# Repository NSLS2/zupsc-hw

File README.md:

# ZuPSC – NSLS-II Power Supply Controller

The **ZuPSC** is the next-generation NSLS-II Power Supply Controller built on a Zynq UltraScale+ FPGA platform. It combines FPGA-based real-time control with embedded software to deliver high-performance regulation, data acquisition, and system diagnostics.
<p align="center">
  <br>
  <em>ZuPSC chassis showing FPGA processing board and channel electronics</em>
</p>

---

## Overview

- **FPGA (PL)**  
  - Executes PID control loops at the sample rate  
  - Handles high-speed data acquisition  
  - Implements interlock and protection logic  

- **ARM Processor (PS)**  
  - Runs a server interface  
  - Communicates with a custom EPICS driver  
  - Provides control, monitoring, and diagnostics over the controls network  

---

## System Architecture

The ZuPSC chassis is composed of three primary circuit boards:

### 1. FPGA Processing Board (zuDFE)
- NSLS-II standard processing platform  
- Digital I/O and GPIO handling  
- ADC data acquisition  
- 20-bit precision DAC output  
- PID control loop execution in FPGA fabric  
- High-speed and low-speed communication:
  - Ethernet
  - Fiber links  
- Embedded Event Receiver (EVR)
  - Compatible with 2.5 Gbps MRF Event Generator (EVG)

---

### 2. Carrier Board
- Interfaces FPGA processing board to channel electronics  
- Routes signals between digital and analog domains  
- Provides system-level connectivity  

---

### 3. Channel Electronics Board
- Precision analog front-end  
- **20-bit DAC** for power supply command output  
- **Dual 20-bit ADCs** for DCCT readback  
- **4× 16-bit ADCs** for auxiliary monitoring  
- Isolated digital I/O channels  

---

## Key Features

- Real-time PID control implemented in FPGA  
- High-resolution (20-bit) DAC/ADC signal chain  
- Deterministic timing via embedded EVR  
- Integrated interlock and protection logic  
- EPICS-compatible control interface  
- Modular 3-board architecture  

---

## Intended Use

The ZuPSC is designed for high-performance accelerator power supply control applications at NSLS-II, where deterministic timing, precision measurement, and reliable interlocks are critical.

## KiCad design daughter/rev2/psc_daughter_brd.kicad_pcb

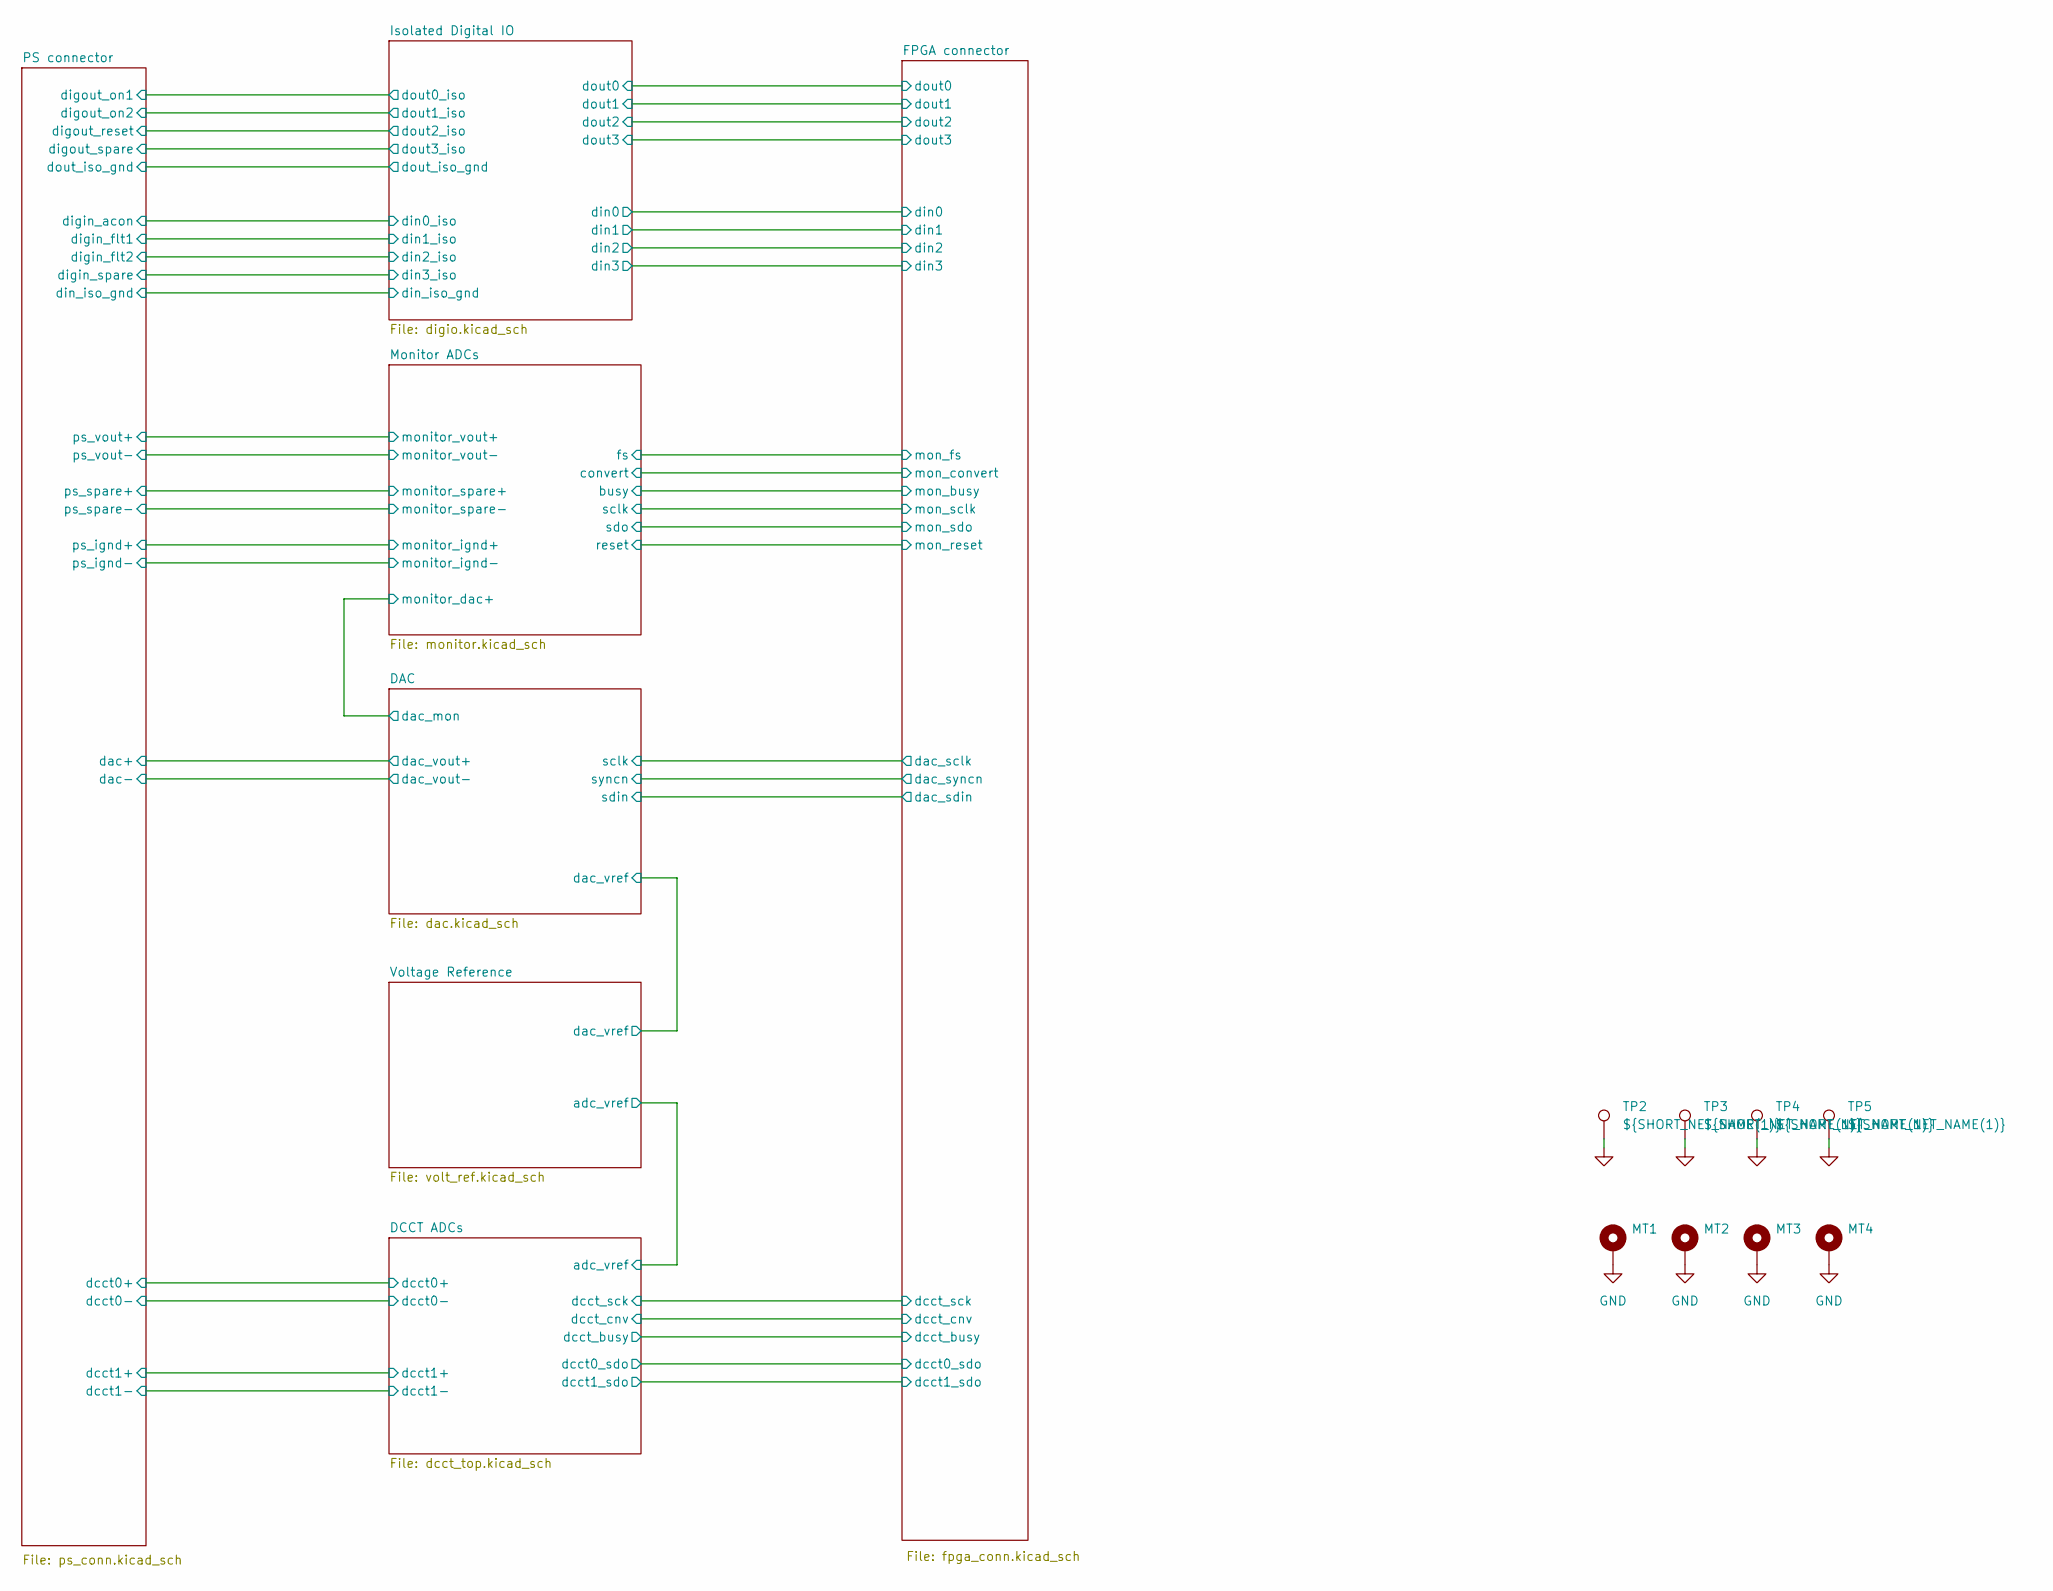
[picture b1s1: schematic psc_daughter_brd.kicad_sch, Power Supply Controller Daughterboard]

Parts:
MT1, MT2, MT3, MT4: MountingHole_Pad; MountingHole_3.2mm_M3_Pad_TopBottom
TP2, TP3, TP4, TP5: ${SHORT_NET_NAME(1)}; TestPoint_RCS-0C; MFG_PN RCS-0C

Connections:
GND: MT1.1, MT2.1, MT3.1, MT4.1, TP2.1, TP3.1, TP4.1, TP5.1; also elsewhere on the board

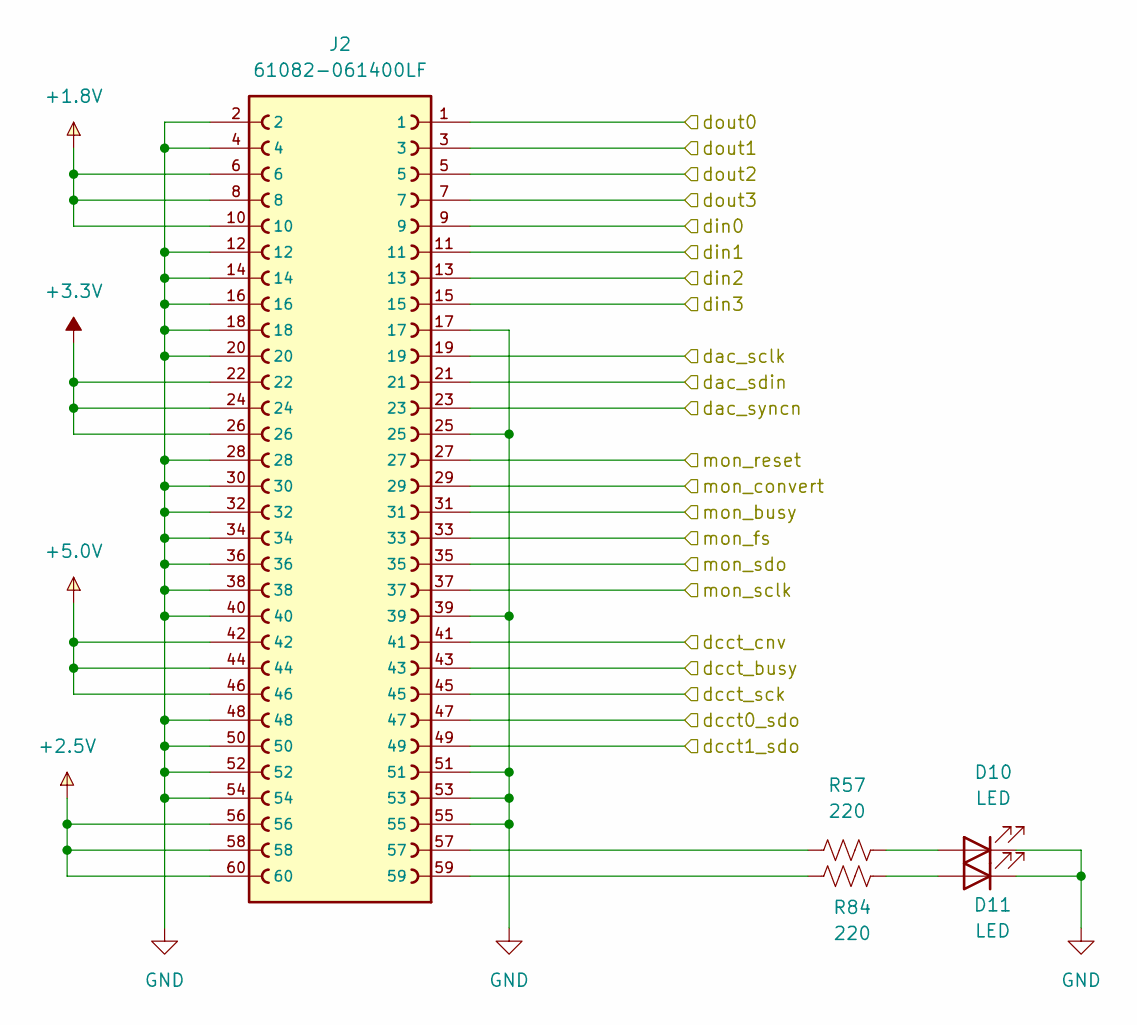
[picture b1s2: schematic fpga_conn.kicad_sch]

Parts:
D10, D11: LED; LED_0603_1608Metric
J2: 61082-061400LF; AMPHENOL_61082-061400LF; PARTREV AS
R57, R84: 220; R_0603_1608Metric; Tolerance 1%; MFG_PN ERJ-3EKF2200V

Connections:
+1.8V: J2.6, J2.8, J2.10; also elsewhere on the board
+2.5V: J2.56, J2.58, J2.60; also elsewhere on the board
+3.3V: J2.22, J2.24, J2.26; also elsewhere on the board
+5.0V: J2.42, J2.44, J2.46; also elsewhere on the board
/DAC/sclk: J2.19; also elsewhere on the board
/DAC/sdin: J2.21; also elsewhere on the board
/DAC/syncn: J2.23; also elsewhere on the board
/DCCT ADCs/dcct0_sdo: J2.47; also elsewhere on the board
/DCCT ADCs/dcct1_sdo: J2.49; also elsewhere on the board
/DCCT ADCs/dcct_busy: J2.43; also elsewhere on the board
/DCCT ADCs/dcct_cnv: J2.41; also elsewhere on the board
/DCCT ADCs/dcct_sck: J2.45; also elsewhere on the board
/FPGA connector/din0: J2.9; also elsewhere on the board
/FPGA connector/din1: J2.11; also elsewhere on the board
/FPGA connector/din2: J2.13; also elsewhere on the board
/FPGA connector/din3: J2.15; also elsewhere on the board
/FPGA connector/dout0: J2.1; also elsewhere on the board
/FPGA connector/dout1: J2.3; also elsewhere on the board
/FPGA connector/dout2: J2.5; also elsewhere on the board
/FPGA connector/dout3: J2.7; also elsewhere on the board
/FPGA connector/mon_busy: J2.31; also elsewhere on the board
/FPGA connector/mon_convert: J2.29; also elsewhere on the board
/FPGA connector/mon_fs: J2.33; also elsewhere on the board
/FPGA connector/mon_reset: J2.27; also elsewhere on the board
/FPGA connector/mon_sclk: J2.37; also elsewhere on the board
/FPGA connector/mon_sdo: J2.35; also elsewhere on the board
GND: D10.1 (K), D11.1 (K), J2.2, J2.4, J2.12, J2.14, J2.16, J2.17, J2.18, J2.20, J2.25, J2.28, J2.30, J2.32, J2.34, J2.36, J2.38, J2.39, J2.40, J2.48, J2.50, J2.51, J2.52, J2.53, J2.54, J2.55; also elsewhere on the board
unnamed: D10.2 (A), R57.2
unnamed: D11.2 (A), R84.2
unnamed: J2.57, R57.1
unnamed: J2.59, R84.1

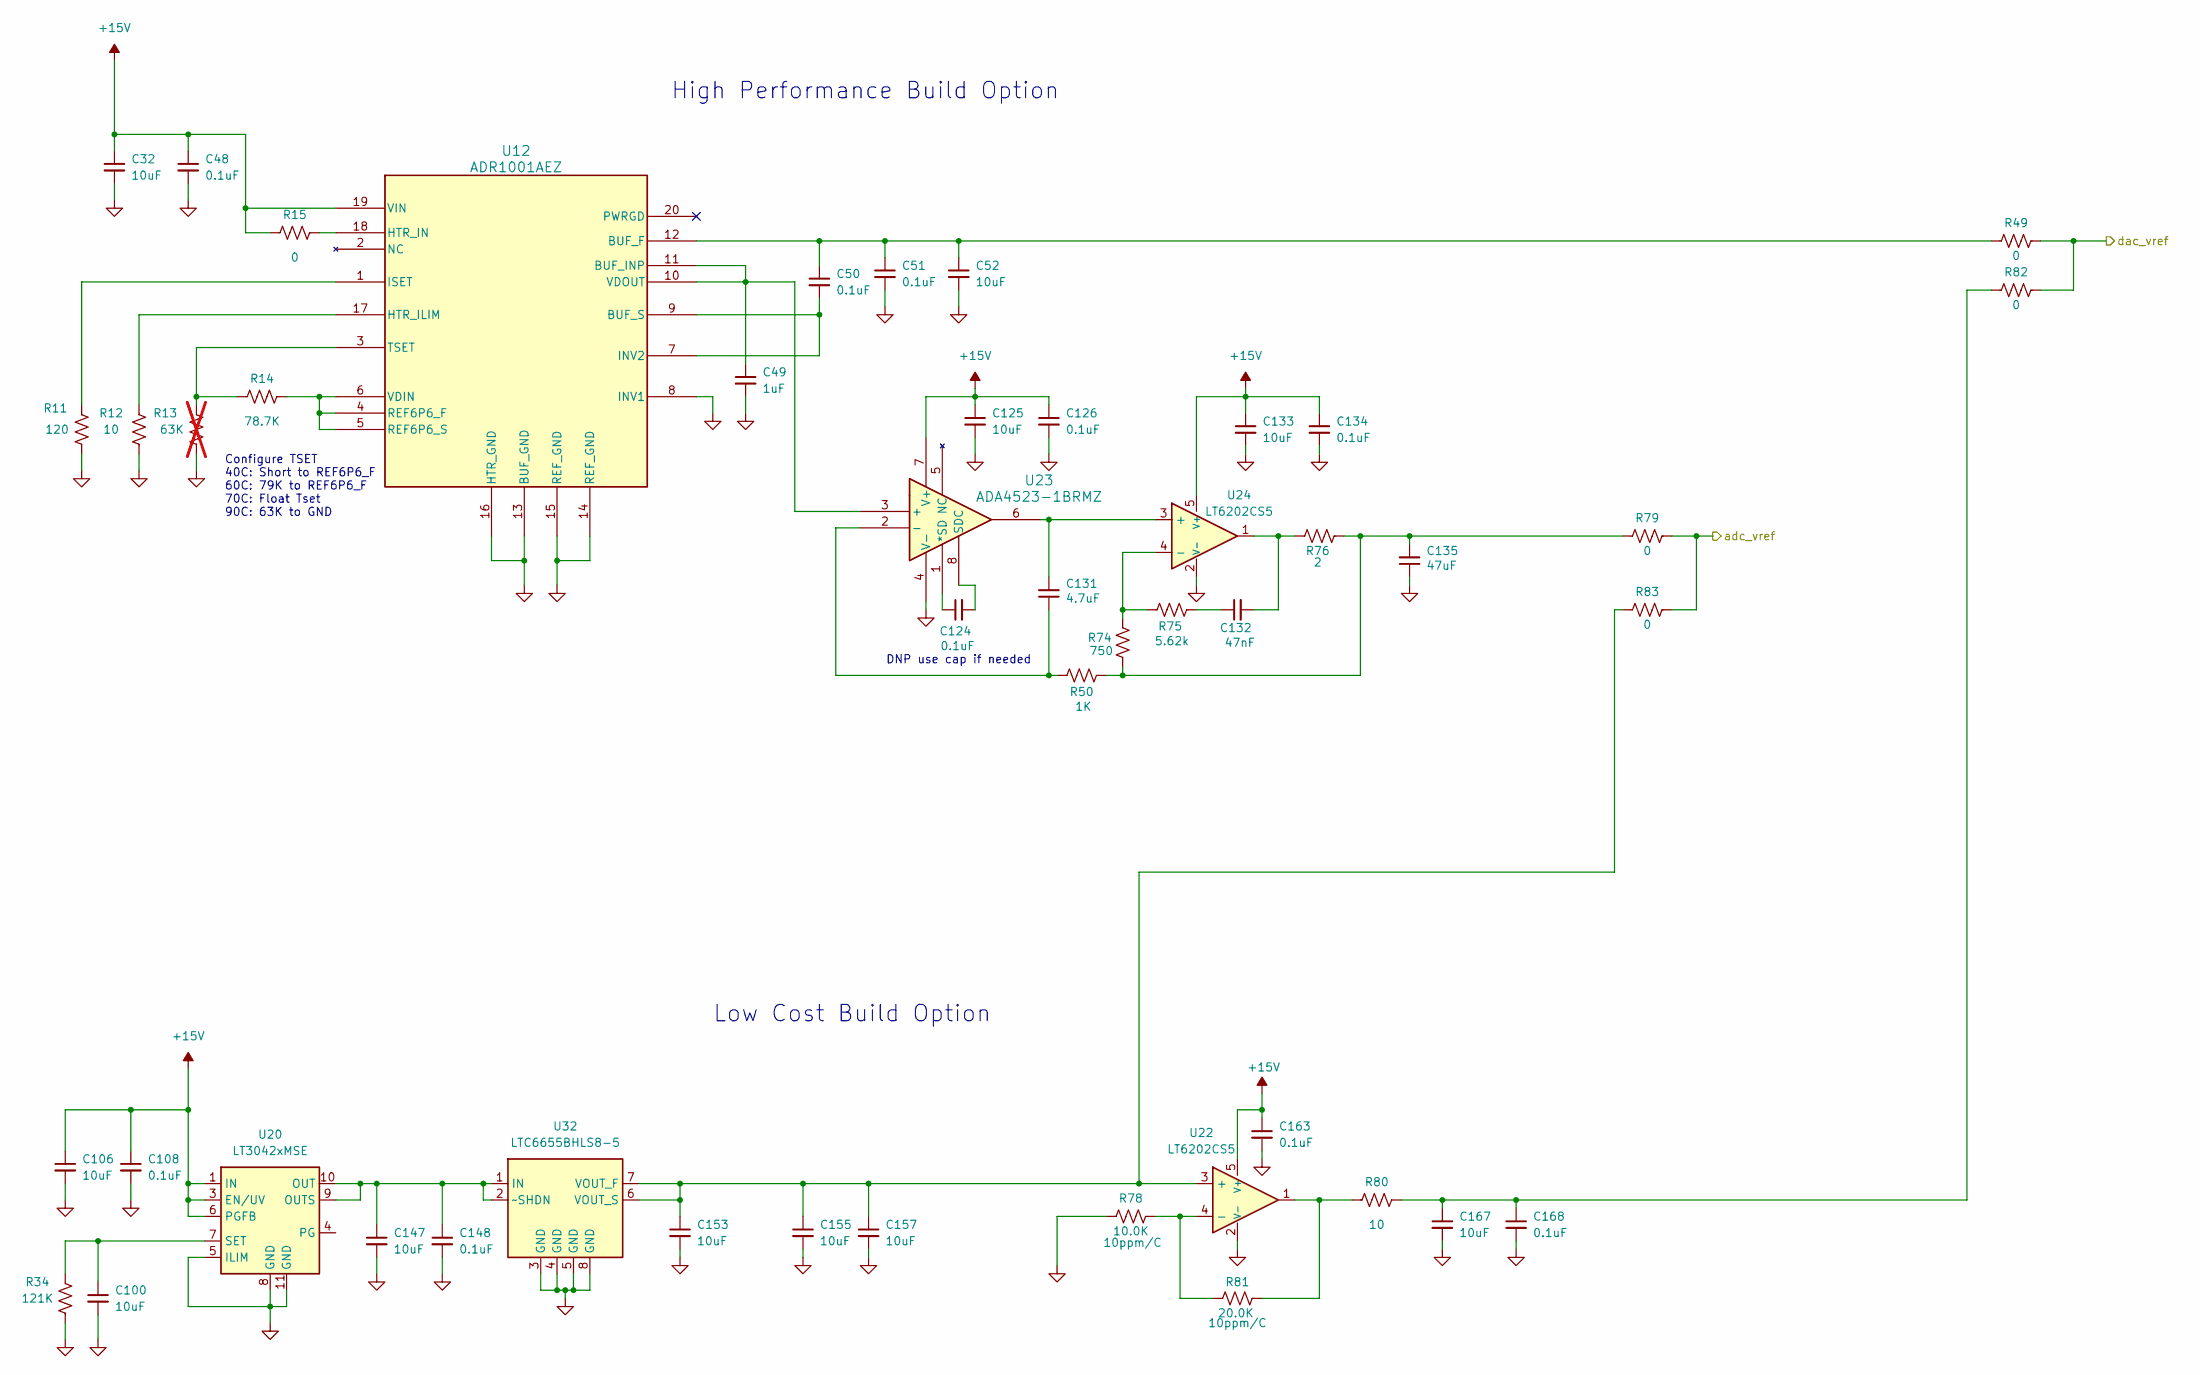
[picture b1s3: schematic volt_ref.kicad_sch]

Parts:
C32, C52, C100, C106, C125, C133, C147, C153, C155, C157, C167: 10uF; C_0603_1608Metric; Voltage 25V; MFG_PN CL10A106MA8NRNC
C48, C50, C51, C108, C124, C126, C134, C148, C163, C168: 0.1uF; C_0402_1005Metric; MFG_PN TMK105BJ104KV-F
C49: 1uF; C_0603_1608Metric; Voltage 25V; MFG_PN CL10B105KA8NNNC
C131: 4.7uF; C_0402_1005Metric; MFG_PN CGA4J1X7R1H475K125AC
C132: 47nF; C_0402_1005Metric; MFG_PN GRM155R71E473KA88D
C135: 47uF; C_1210_3225Metric; MFG_PN MSAST32MAB5476MPNDT1
R11: 120; R_0402_1005Metric; Tolerance 1%; MFG_PN ERJ-2RKF1200X
R12, R80: 10; R_0402_1005Metric; Tolerance 1%; MFG_PN ERJ-2RKF10R0X
R13: 63K; R_0402_1005Metric; Tolerance 1%; MFG_PN ERJ-2RKF6342X; not fitted
R14: 78.7K; R_0402_1005Metric; Tolerance 1%; MFG_PN ERJ-2RKF7872X
R15, R49, R79, R82, R83: 0; R_0402_1005Metric; Tolerance 1%; MFG_PN ERJ-2GE0R00X
R34: 121K; R_0402_1005Metric; Tolerance 1%; MFG_PN ERJ-2RKF1213X
R50: 1K; R_0402_1005Metric; Tolerance 0.1%; MFG_PN ERA-2ARB102X
R74: 750; R_0402_1005Metric; Tolerance 1%; MFG_PN ERA-2ARB751X
R75: 5.62k; R_0402_1005Metric; Tolerance 0.1%; MFG_PN ERA-2ARB5621X
R76: 2; R_0402_1005Metric; Tolerance 0.1%; MFG_PN RNCA0805BTS2K00
R78: 10.0K; R_0603_1608Metric; Tolerance 0.1%; MFG_PN RT0603BRB0710KL
R81: 20.0K; R_0603_1608Metric; Tolerance 0.1%; MFG_PN ERA-3ARB203V
U12: ADR1001AEZ; E-20-1_ADI; MFG_PN ADR1001AEZ
U20: LT3042xMSE; MSOP-10-1EP_3x3mm_P0.5mm_EP1.68x1.88mm; MFG_PN LT3042EMSE#TRPBF
U22, U24: LT6202CS5; MFG_PN LT6202CS5#TRPBF
U23: ADA4523-1BRMZ; RM-8_ADI; MFG_PN ADA4523-1BRMZ
U32: LTC6655BHLS8-5; LTC6655; MFG_PN LTC6655BHLS8-5#PBF

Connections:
+15V: C32.1, C48.1, C106.1, C108.1, C125.1, C126.1, C133.1, C134.1, C163.1, R15.2, U12.19 (VIN), U20.1 (IN), U20.2 (IN), U20.3 (EN/UV), U20.6 (PGFB), U22.5 (V+), U23.7 (V+), U24.5 (V+); also elsewhere on the board
/DAC/dac_vref: R49.1, R82.1; also elsewhere on the board
/DCCT ADCs/adc_vref: R79.1, R83.1; also elsewhere on the board
GND: C32.2, C48.2, C49.2, C51.2, C52.2, C100.2, C106.2, C108.2, C125.2, C126.2, C133.2, C134.2, C135.1, C147.2, C148.2, C153.2, C155.2, C157.2, C163.2, C167.2, C168.2, R11.1, R12.1, R13.1, R34.1, R78.2, U12.8 (INV1), U12.13 (BUF_GND), U12.14 (REF_GND), U12.15 (REF_GND), U12.16 (HTR_GND), U20.5 (ILIM), U20.8 (GND), U20.11 (GND), U22.2 (V-), U23.4 (V-), U24.2 (V-), U32.3 (GND), U32.4 (GND), U32.5 (GND), U32.8 (GND); also elsewhere on the board
unnamed: C132.1, R75.1
unnamed: C132.2, R76.2, U24.1
unnamed: C135.2, R50.1, R74.1, R76.1, R79.2
unnamed: C167.1, C168.1, R80.1, R82.2
unnamed: R80.2, R81.2, U22.1
unnamed: C50.1, C51.1, C52.1, R49.2, U12.12 (BUF_F)
unnamed: C49.1, U12.10 (VDOUT), U12.11 (BUF_INP), U23.3 (+)
unnamed: C50.2, U12.7 (INV2), U12.9 (BUF_S)
unnamed: R12.2, U12.17 (HTR_ILIM)
unnamed: R15.1, U12.18 (HTR_IN)
unnamed: R11.2, U12.1 (ISET)
unnamed: R14.1, U12.4 (REF6P6_F), U12.5 (REF6P6_S), U12.6 (VDIN)
unnamed: R13.2, R14.2, U12.3 (TSET)
unnamed: C147.1, C148.1, U20.9 (OUTS), U20.10 (OUT), U32.1 (IN), U32.2 (~SHDN)
unnamed: C100.1, R34.2, U20.7 (SET)
unnamed: C153.1, C155.1, C157.1, R83.2, U22.3 (+), U32.6 (VOUT_S), U32.7 (VOUT_F)
unnamed: R78.1, R81.1, U22.4 (-)
unnamed: C124.1, U23.1 (*SD)
unnamed: C131.1, R50.2, U23.2 (-)
unnamed: C124.2, U23.8 (SDC)
unnamed: C131.2, U23.6, U24.3 (+)
unnamed: R74.2, R75.2, U24.4 (-)

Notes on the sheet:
Configure TSET 40C: Short to REF6P6_F 60C: 79K to REF6P6_F 70C: Float Tset 90C: 63K to GND
High Performance Build Option
DNP use cap if needed
Low Cost Build Option

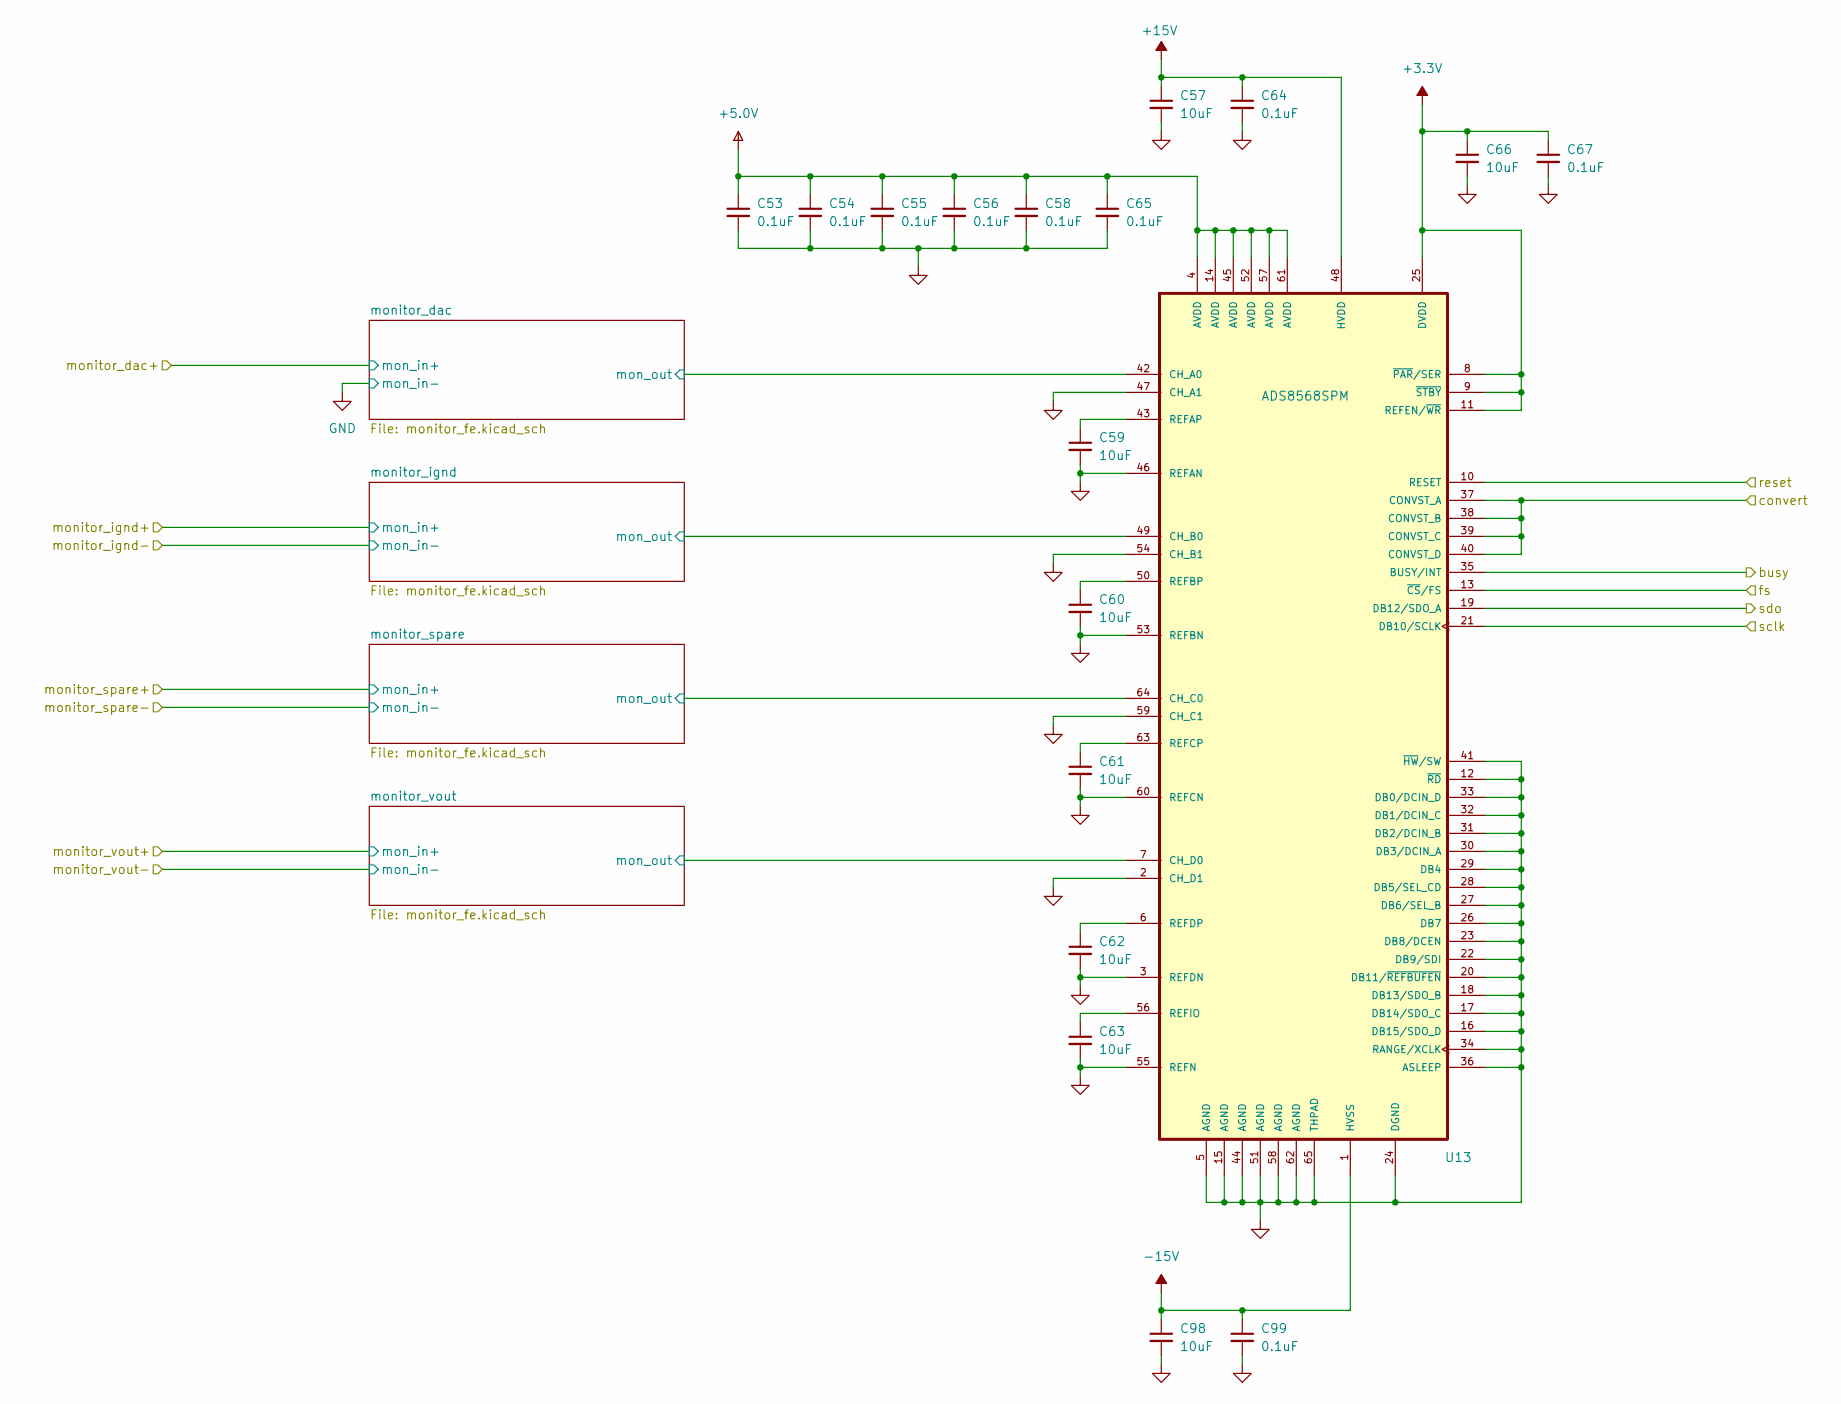
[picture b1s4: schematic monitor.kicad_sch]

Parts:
C53, C54, C55, C56, C58, C64, C65, C67, C99: 0.1uF; C_0402_1005Metric; MFG_PN TMK105BJ104KV-F
C57, C59, C60, C61, C62, C63, C66, C98: 10uF; C_0603_1608Metric; Voltage 25V; MFG_PN CL10A106MA8NRNC
U13: ADS8568SPM; QFP50P1200X1200X160-64N; MFG_PN ADS8568SPM

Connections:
+3.3V: C66.1, C67.1, U13.8 (~PAR/SER), U13.9 (~STBY), U13.11 (REFEN/~WR), U13.25 (DVDD); also elsewhere on the board
+5.0V: C53.1, C54.1, C55.1, C56.1, C58.1, C65.1, U13.4 (AVDD), U13.14 (AVDD), U13.45 (AVDD), U13.52 (AVDD), U13.57 (AVDD), U13.61 (AVDD); also elsewhere on the board
+15V: C57.1, C64.1, U13.48 (HVDD); also elsewhere on the board
-15V: C98.1, C99.1, U13.1 (HVSS); also elsewhere on the board
/FPGA connector/mon_busy: U13.35 (BUSY/INT); also elsewhere on the board
/FPGA connector/mon_convert: U13.37 (CONVST_A), U13.38 (CONVST_B), U13.39 (CONVST_C), U13.40 (CONVST_D); also elsewhere on the board
/FPGA connector/mon_fs: U13.13 (~CS/FS); also elsewhere on the board
/FPGA connector/mon_reset: U13.10 (RESET); also elsewhere on the board
/FPGA connector/mon_sclk: U13.21 (DB10/SCLK); also elsewhere on the board
/FPGA connector/mon_sdo: U13.19 (DB12/SDO_A); also elsewhere on the board
/Monitor ADCs/monitor_dac/mon_out: U13.42 (CH_A0); also elsewhere on the board
/Monitor ADCs/monitor_ignd/mon_out: U13.49 (CH_B0); also elsewhere on the board
/Monitor ADCs/monitor_spare/mon_out: U13.64 (CH_C0); also elsewhere on the board
/Monitor ADCs/monitor_vout/mon_out: U13.7 (CH_D0); also elsewhere on the board
GND: C53.2, C54.2, C55.2, C56.2, C57.2, C58.2, C59.2, C60.2, C61.2, C62.2, C63.2, C64.2, C65.2, C66.2, C67.2, C98.2, C99.2, U13.2 (CH_D1), U13.3 (REFDN), U13.5 (AGND), U13.12 (~RD), U13.15 (AGND), U13.16 (DB15/SDO_D), U13.17 (DB14/SDO_C), U13.18 (DB13/SDO_B), U13.20 (DB11/~REFBUFEN), U13.22 (DB9/SDI), U13.23 (DB8/DCEN), U13.24 (DGND), U13.26 (DB7), U13.27 (DB6/SEL_B), U13.28 (DB5/SEL_CD), U13.29 (DB4), U13.30 (DB3/DCIN_A), U13.31 (DB2/DCIN_B), U13.32 (DB1/DCIN_C), U13.33 (DB0/DCIN_D), U13.34 (RANGE/XCLK), U13.36 (ASLEEP), U13.41 (~HW/SW), U13.44 (AGND), U13.46 (REFAN), U13.47 (CH_A1), U13.51 (AGND), U13.53 (REFBN), U13.54 (CH_B1), U13.55 (REFN), U13.58 (AGND), U13.59 (CH_C1), U13.60 (REFCN), U13.62 (AGND), U13.65 (THPAD); also elsewhere on the board
unnamed: C59.1, U13.43 (REFAP)
unnamed: C60.1, U13.50 (REFBP)
unnamed: C61.1, U13.63 (REFCP)
unnamed: C62.1, U13.6 (REFDP)
unnamed: C63.1, U13.56 (REFIO)

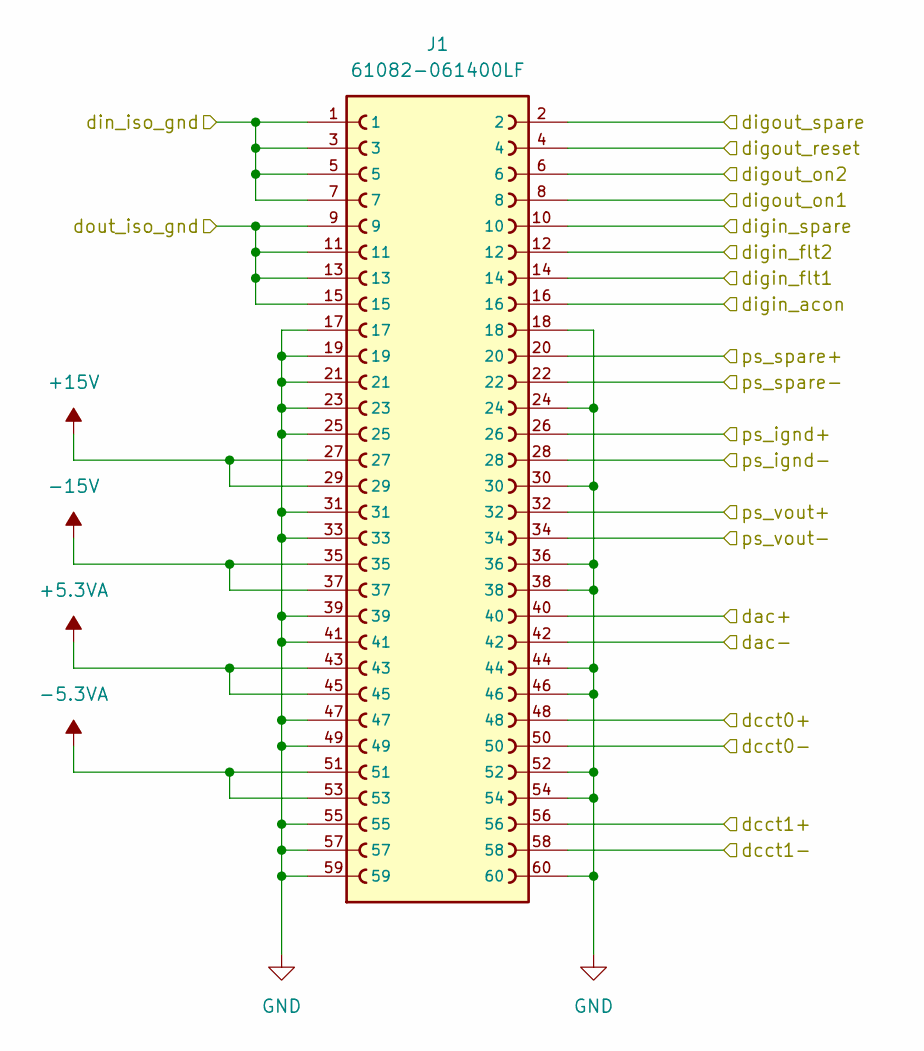
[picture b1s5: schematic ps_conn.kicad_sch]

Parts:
J1: 61082-061400LF; AMPHENOL_61082-061400LF; PARTREV AS

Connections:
+5.3VA: J1.43, J1.45; also elsewhere on the board
+15V: J1.27, J1.29; also elsewhere on the board
-5.3VA: J1.51, J1.53; also elsewhere on the board
-15V: J1.35, J1.37; also elsewhere on the board
/DAC/dac_vout+: J1.40; also elsewhere on the board
/DAC/dac_vout-: J1.42; also elsewhere on the board
/DCCT ADCs/dcct0+: J1.48; also elsewhere on the board
/DCCT ADCs/dcct0-: J1.50; also elsewhere on the board
/DCCT ADCs/dcct1+: J1.56; also elsewhere on the board
/DCCT ADCs/dcct1-: J1.58; also elsewhere on the board
/Isolated Digital IO/din0_iso: J1.16; also elsewhere on the board
/Isolated Digital IO/din1_iso: J1.14; also elsewhere on the board
/Isolated Digital IO/din2_iso: J1.12; also elsewhere on the board
/Isolated Digital IO/din3_iso: J1.10; also elsewhere on the board
/Isolated Digital IO/din_iso_gnd: J1.1, J1.3, J1.5, J1.7; also elsewhere on the board
/Isolated Digital IO/dout0_iso: J1.8; also elsewhere on the board
/Isolated Digital IO/dout1_iso: J1.6; also elsewhere on the board
/Isolated Digital IO/dout2_iso: J1.4; also elsewhere on the board
/Isolated Digital IO/dout3_iso: J1.2; also elsewhere on the board
/Isolated Digital IO/dout_iso_gnd: J1.9, J1.11, J1.13, J1.15; also elsewhere on the board
/Monitor ADCs/monitor_ignd+: J1.26; also elsewhere on the board
/Monitor ADCs/monitor_ignd-: J1.28; also elsewhere on the board
/Monitor ADCs/monitor_spare+: J1.20; also elsewhere on the board
/Monitor ADCs/monitor_spare-: J1.22; also elsewhere on the board
/Monitor ADCs/monitor_vout+: J1.32; also elsewhere on the board
/Monitor ADCs/monitor_vout-: J1.34; also elsewhere on the board
GND: J1.17, J1.18, J1.19, J1.21, J1.23, J1.24, J1.25, J1.30, J1.31, J1.33, J1.36, J1.38, J1.39, J1.41, J1.44, J1.46, J1.47, J1.49, J1.52, J1.54, J1.55, J1.57, J1.59, J1.60; also elsewhere on the board

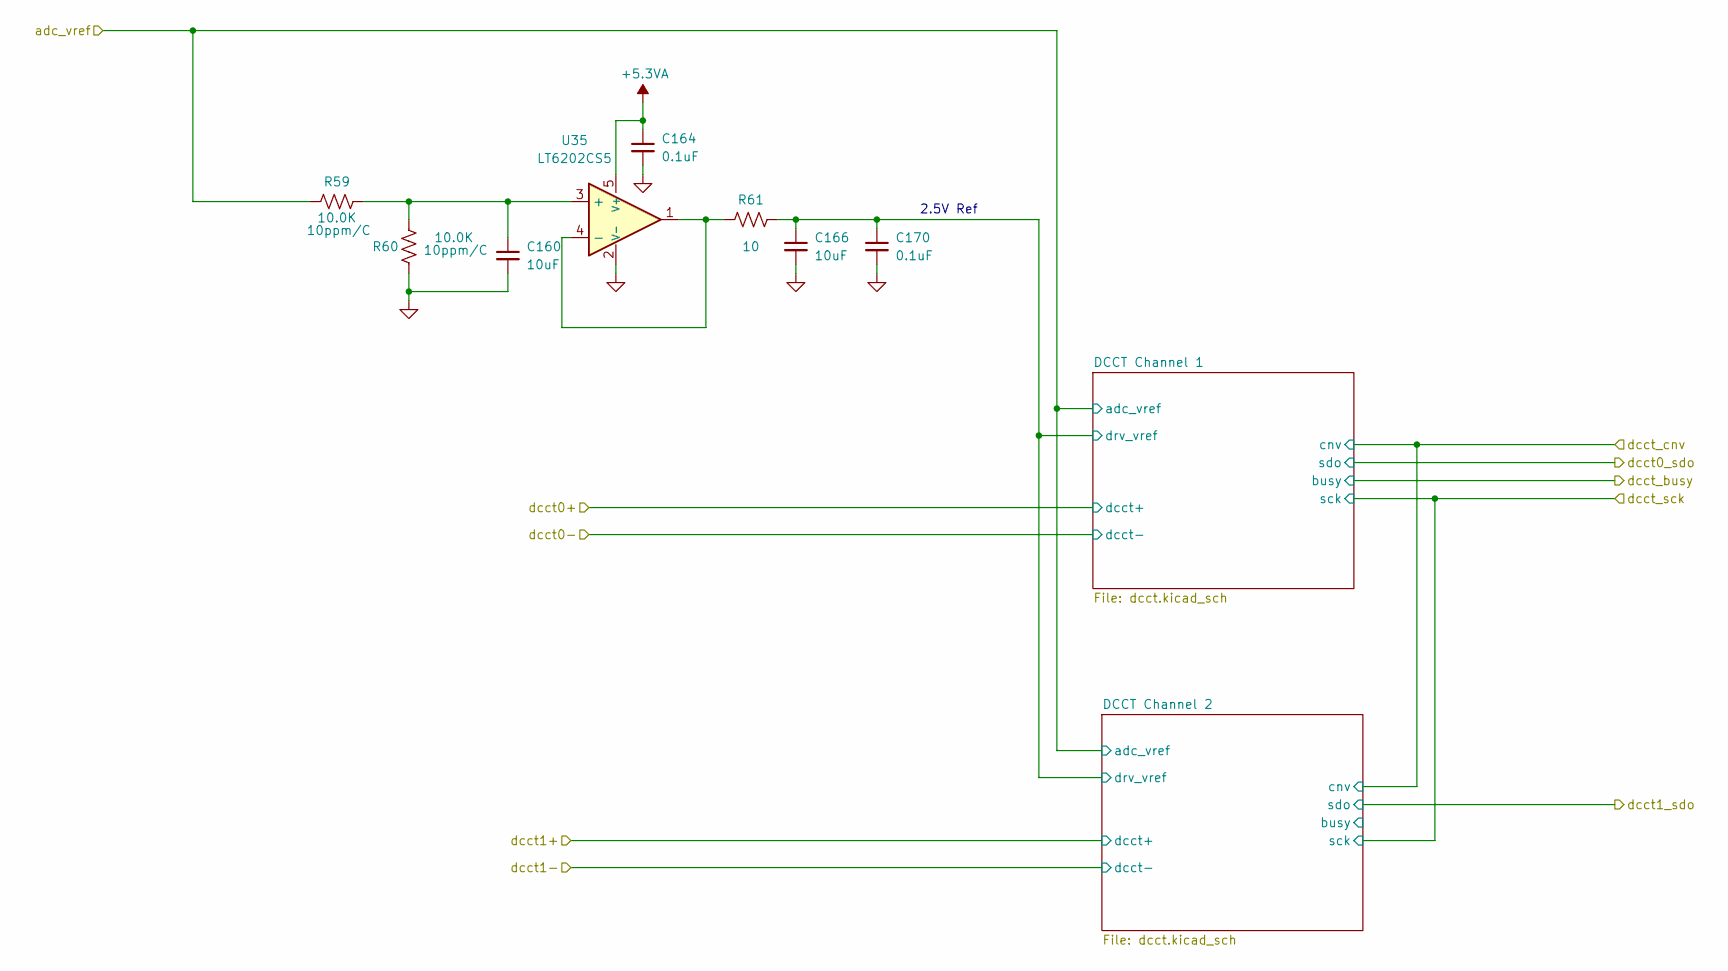
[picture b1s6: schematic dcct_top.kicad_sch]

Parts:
C160, C166: 10uF; C_0603_1608Metric; Voltage 25V; MFG_PN CL10A106MA8NRNC
C164, C170: 0.1uF; C_0402_1005Metric; MFG_PN TMK105BJ104KV-F
R59, R60: 10.0K; R_0603_1608Metric; Tolerance 0.1%; MFG_PN RT0603BRB0710KL
R61: 10; R_0402_1005Metric; Tolerance 1%; MFG_PN ERJ-2RKF10R0X
U35: LT6202CS5; MFG_PN LT6202CS5#TRPBF

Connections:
+5.3VA: C164.1, U35.5 (V+); also elsewhere on the board
/DCCT ADCs/DCCT Channel 1/drv_vref: C166.1, C170.1, R61.1; also elsewhere on the board
/DCCT ADCs/adc_vref: R59.2; also elsewhere on the board
GND: C160.2, C164.2, C166.2, C170.2, R60.1, U35.2 (V-); also elsewhere on the board
unnamed: C160.1, R59.1, R60.2, U35.3 (+)
unnamed: R61.2, U35.1, U35.4 (-)

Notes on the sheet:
2.5V Ref
